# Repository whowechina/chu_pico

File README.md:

# Chu Pico - Chunithm Style Mini Controller
[点这里可以切换到中文版](README_CN.md)

Features:
* It's small, made for 15-17 inch screen.
* Air towers are replaced with built-in ToF sensors.
* Traditional IR Air mechanism is also provided for DIYers.
* HID lights, of course!
* 32 keys (upper and lower rows).
* Follows CrazyRedMachine's RedBoard I/O protocol.
* Command line of rich features.
* All source files open.

Thanks to many respectful guys/companies who made their tools or materials free or open source (KiCad, OnShape, InkScape, Raspberry things).

And thanks to community developers that inspired me and helped me: CrazyRedMachine (https://github.com/CrazyRedMachine), SpeedyPotato (https://github.com/speedypotato).

And also:
* RP_Silicon_KiCad: https://github.com/HeadBoffin/RP_Silicon_KiCad
* Type-C: https://github.com/ai03-2725/Type-C.pretty

## My Other Projects
You can check out my other cool projects.

* Popn Pico: https://github.com/whowechina/popn_pico
* IIDX Pico: https://github.com/whowechina/iidx_pico
* Chu Pico: https://github.com/whowechina/chu_pico
* Mai Pico: https://github.com/whowechina/mai_pico
* Diva Pico: https://github.com/whowechina/diva_pico
* AIC Pico: https://github.com/whowechina/aic_pico
* Groove Pico: https://github.com/whowechina/groove_pico
* Geki Pico: https://github.com/whowechina/geki_pico
* Musec Pico: https://github.com/whowechina/musec_pico
* Ju Pico: https://github.com/whowechina/ju_pico
* Bishi Pico: https://github.com/whowechina/bishi_pico
* Nos Pico: https://github.com/whowechina/nos_pico
* Voltex Pico: https://github.com/whowechina/voltex_pico
* Chord Pico: https://github.com/whowechina/chord_pico
* Dance Pico: https://github.com/whowechina/dance_pico
* Arcade Pico: https://github.com/whowechina/arcade_pico

## **Disclaimer** ##
I made this project in my personal time with no financial benefit or sponsorship. I will continue to improve the project. I have done my best to ensure that everything is accurate and functional, there's always a chance that mistakes may occur. I cannot be held responsible for any loss of your time or money that may result from using this open source project. Thank you for your understanding.

## About the License
It's CC-NC. So DIY for yourself and for your friend, don't make money from it. And plagiarism that doesn’t even dare to mention the original author is not acceptable. Please note that pooling orders and group buying for raw materials is acceptable.Selling any leftover components at cost (without profit) is also acceptable.

If you're interested in buying from me, or for commercial use, please contact me (Discord, QQ group, Goofish).
* My Discord Invitation: https://discord.gg/M8f2PPQFEA
* QQ Group: 854535476
* Goofish: whowe12345

## HOW TO BUILD
### Frequently Made Mistakes
Many DIY enthusiasts commonly make certain mistakes during the building process. Please proceed with extra caution to avoid these.
* **MISTAKE: Soldering everything together without conducting intermediate testing.**  
  Remember, even professional engineers can make mistakes. It becomes significantly harder to identify the root cause of a problem when all components are already assembled or soldered. Therefore, it's advisable to solder and test in stages. The firmware is designed to function correctly even with some components missing, which is good for testing.
* **MISTAKE: Neglecting to cut the ADDR pin trace on the MPR121 module.**  
  The MPR121 module in the market has the ADDR pin pre-connected to ground. But the board expects a floating ADDR pin, otherwise the ADDR pin will short the circuit. Please verify your "CUT" using a multimeter.
* **MISTAKE: Rushing to replace components when something fails.**  
  Sometimes people prematurely assumes that the Raspberry Pi Pico or other modules are faulty.
  Be aware that desoldering and soldering large SMD components is a challenging task. It carries the risk of damaging the component or the PCB board. Patience and caution are crucial. Look at the schematics and PCB design files and ask help from community first. Questioning the integrity of these components should be your last resort.
* **MISTAKE: Failing to properly solder the 2 USB pins of the Raspberry Pi Pico.**  
  These pins are at the bottom side of the PCB. It's a common oversight to either forget to solder them or to leave air bubbles during the process. To avoid this, solder slowly from one side of the hole, using minimal solder wire and a generous amount of flux.

### PCB
* Go JLCPCB and make order with the gerber zip file (latest `Production\PCB\chu_main_xxx.zip`), regular FR-4 board, black color, thickness is **1.6mm**.  
* 1x Rasberry Pico Pi Pico or Pico W.  
  https://www.raspberrypi.com/products/raspberry-pi-pico
  Becareful of 3 pins that are at the other side, they're difficult to solder and may leave air bubbles.  

* 1x USB Type-C socket (918-418K2023S40001 or KH-TYPE-C-16P)
* 36x WS2812B-4020 side-facing RGB LEDs.  
  https://www.lcsc.com/product-detail/Light-Emitting-Diodes-LED_Worldsemi-WS2812B-4020_C965557.html
* TCA9548APWR (TSSOP-24) I2C multiplexer.  
  https://www.lcsc.com/product-detail/Signal-Switches-Encoders-Decoders-Multiplexers_Texas-Instruments-TCA9548APWR_C130026.html
* 3x MPR121 modules, there're many types in the market, choose ones like this.  
  https://www.sparkfun.com/products/retired/9695  
  Before solder MP121 module to the main PCB board, remember to use a knife to **cut (unshort) the tiny trace that connects ADDR to the GND**. Please be careful not to cut more than necessary.  
    
  There's not enough space for the whole height of MPR121 module plus the lead pads. So you need to solder the module like the picture shows below.  
  First apply some insulation tape.  
    
  Then solder the module directly against the PCB.  
    
  You can use the pins comes with the module, but you need to cut away the plastic pads.  
  
* 5x Sharp GP2Y0E03 or ST VL53L0X ToF sensor modules, you need cables as well. Please note that the pictures are taken from older version of PCB, the LEDs have been changed to side-facing ones.  
  https://www.lcsc.com/product-detail/Angle-Linear-Position-Sensors_Sharp-Microelectronics-GP2Y0E03_C920270.html  

   You can use both of them in a same PCB, the firmware will identify each of them automatically.  
  
* 12x 0603 5.1kohm resistors for all the resistors on PCB.
* 8x 0603 1uF (0.1~1uF all fine) capacitors (C1 to C8), OPTIONAL, recommended.
* 3x Panasonic EVQP46B3M tiny tactile switches.  
  https://industry.panasonic.com/global/en/products/control/switch/light-touch/number/evqp46b3m

### Light Guide Panel
* Find a service to cut a light guide panel using DXF or DWG file `Production\CAD\chu_pico_lgp.*`, the size is 256mm*60mm, 1.8mm to 2.0mm thickness, thinner is better for sensitivity. 2.0mm is easy to find, 1.8mm is rare. I used 1.8mm for my build.  
  
* LGP material choices:
  * Real LGP (Light Guide Panel) material, it's the best choice.  
    
  * Clear Acrylic with Light Guide Film, it's a good choice.  
    
  * Clear Acrylic with single-side-frosted, it's a good choice.  
    
  * Clear Acrylic with manual single-side-sanding, it can work too.  

### Panel Film
* A self-adhesive **textured**/**frosted** film sheet, it is applied on top surface of the light guide panel. It improves touch feel. You can use window sticker film. It **MUST** be self-adhesive ones, **NOT** static cling ones. They're usually very cheap.
* Cut the film to roughly match the shape of the light guide panel, and stick to the panel.  
  
* Gentlely rub the film to remove any air bubbles and make it stick tightly.  

###  IR Cover
* It's for good looking, as it hides 5 ToF sensors.   
  
* IR lights can go through.  
  
* Find a service to cut an IR cover using the DXF or DWG file `Production\CAD\chu_pico_ir_cover.*`, the size is 293.2mm*63.5mm, 1mm thickness. The material must be "Infrared Transmitting Acrylic Sheet" which can block visible lights (so it looks black) while letting IR lights go through.  
  
* If you can't find one, cut a regular smooth surface acrylic, but it can't hide the ToF sensors which are not good looking.
* If you're using the VL53L0x ToF sensor, please add padding beneath the sensor. This brings it closer to the acrylic cover, which can prevent acrosstalk error.

### 3D Printing
* You need a Bambu 3D printer for 2 reasons:
  * Parts are designed to perfectly fit in its 256mm*256mm print bed.
  * Its AMS system works great for easy-to-remove support material.
* For all the following prints:
  * To fit object in the bed, Z rotate: 315 degree, X, Y move to: 134mm  

  * PLA, PETG, ABS are all OK.
  * Layer height: 0.2mm
  * 4-6 walls, 50+% infill
  * Support: No (unless specified).

* Base: `Production\3D\chu_pico_base.stl`, dark gray filament, turn on support to have better screw holes.
* Cover: `Production\3D\chu_pico_cover(_aime).stl`, dark gray filament, print up-side down.
* Cover Base: `Production\3D\chu_pico_cover_base.stl`, **clear transparent (IMPORTANT)** filament.
* Light Guide Panel Fixer: `Production\3D\chu_pico_lgp_fixer.stl`, color doesn't matter. Note that in newer revisions, it has been integrated into the base.

### Exploded View for Assembly

From top to bottom:
* IR Cover
* Cover
* Cover Base
* Panel Film
* Light Guide Panel
* PCB
* Light Guide Panel Fixer (integrated into the base in newer revisions)
* Base

Notes:
* You need **4x M3\*12mm screws and 4x M3 hex nuts** to fix the housing.
* You need **4x M2\*6mm screws** for extra fixation for the lgp area of the housing.
* If you use the `_insert` version of the cover, you also need **4x M2\*3mm\*3mm heatset inserts**.

7x silicone anti-slip pads can be applied to the bottom side of the base to provide stability when playing.  

### IR Air Tower
This is not necessary for Chu Pico. But some people may prefer the traditional IR air tower, especially when they're using Chu Pico design for a full-sized controller.
So hereby I provide the IR air tower design, with a pair of air tower PCBs and the firmware support.
1. First, you need to order the sensor PCBs, the gerber file is `Production\PCB\chu_air_v*.zip`. It's for both sides of the air tower.
2. Solder components to the PCB following the silkscreen. About the components, see the notes below.
3. For left side PCB, use J1 to connect to the Raspberry Pi Pico, and for the right side PCB, use J2. GPIO 3 -> A, GPIO 4 -> B, GPIO 5 -> C, ADC 0 (GPIO 26) -> Right S, ADC 1 (GPIO 27) -> Left S.  

4. Steps for deployment.
   * Enable IR sensor in the firmware (command `ir enable`), this will disable ToF.
   * Enable diagnostics for IR (command `ir diagnostic`).
   * Orientation of the PCB: for the left side PCB, its J1 is at the lowest, for the right side PCB, its J2 is at the lowest (up-side-down).
   * Place the air towers and watch the output of the diagnostics, higher value means beam is received.
   * Set the baseline after the towers are properly placed (command `ir baseline`).
   * Optionally, set the sensitivity, it's a percentage of expected change (command `ir trigger <1..100>`).

#### Notes for the Components
* D1, D2, D3 are IR333C-A IR LEDs;
* Q2, Q4, Q6 are PT333-3B phototransistors.
* Q1, Q3, Q5 are N-Channel MOSFETs with low Rds, such as AO3400, see calculations below.
* R2, R4, R6 are current limiting resistors, see calculations below.
* R1, R3, R5 are mosfet gate resistors, 10ohm is fine.
* R7, R8, R9 are pull-up resistors, 2Kohm is fine.
* R10 is a pull-down resistor, 10Kohm is fine.

* Let's do the calculation for D1 as an example. To get proper signal strength, we want about 1A current for it.  
  The current for D1 is calculated by `I = (Vcc - Vf) / (Rds + R2)`. Vcc is 3.3V, Vf is the forward voltage of D1 (about 2.6V@1A). For a low Rds N-Channel MOSFET such as AO3400, Rds is about 0.047ohm, so R2 should be about 0.7ohm to get 1A current. You can use other N-Channel MOSFETs, but you need to calculate the values accordingly.

### Firmware
* UF2 file is in `Production\Firmware` folder.
* For the new build, hold the BOOTSEL button while connect the USB to a PC, there will be a disk named "RPI-RP2" showed up. Drag the UF2 firmware binary file into it. That's it. There's a small hole at the bottom side of the Chu Pico, it is facing right to the BOOTSEL button.
* It works on CrazyRedMachine's RedBoard protocol. For more information, please check out CrazyRedMachine's project (Don't forget to give him a star and drop by his GitHub for other cool projects):  
https://github.com/CrazyRedMachine/RedBoard
* It has a command line to do configuration. You can use this Web Serial Terminal to connect to the USB serial port of the Chu Pico. (Note: "?" is for help)  
  https://googlechromelabs.github.io/serial-terminal/  

## CAD Source File
I'm using OnShape free subscription. It's powerful but it can't archive original designs to local, so I can only share the link here. STL/DXF/DWG files are exported from this online document.  
https://cad.onshape.com/documents/8b9d0fe6ff1bfa4da17d33ee/w/5c7c980a282a19e7ba1db795/e/56ee65492584a3f709c23c49?renderMode=1&uiState=64fd606f17393c0e6f9b19a4

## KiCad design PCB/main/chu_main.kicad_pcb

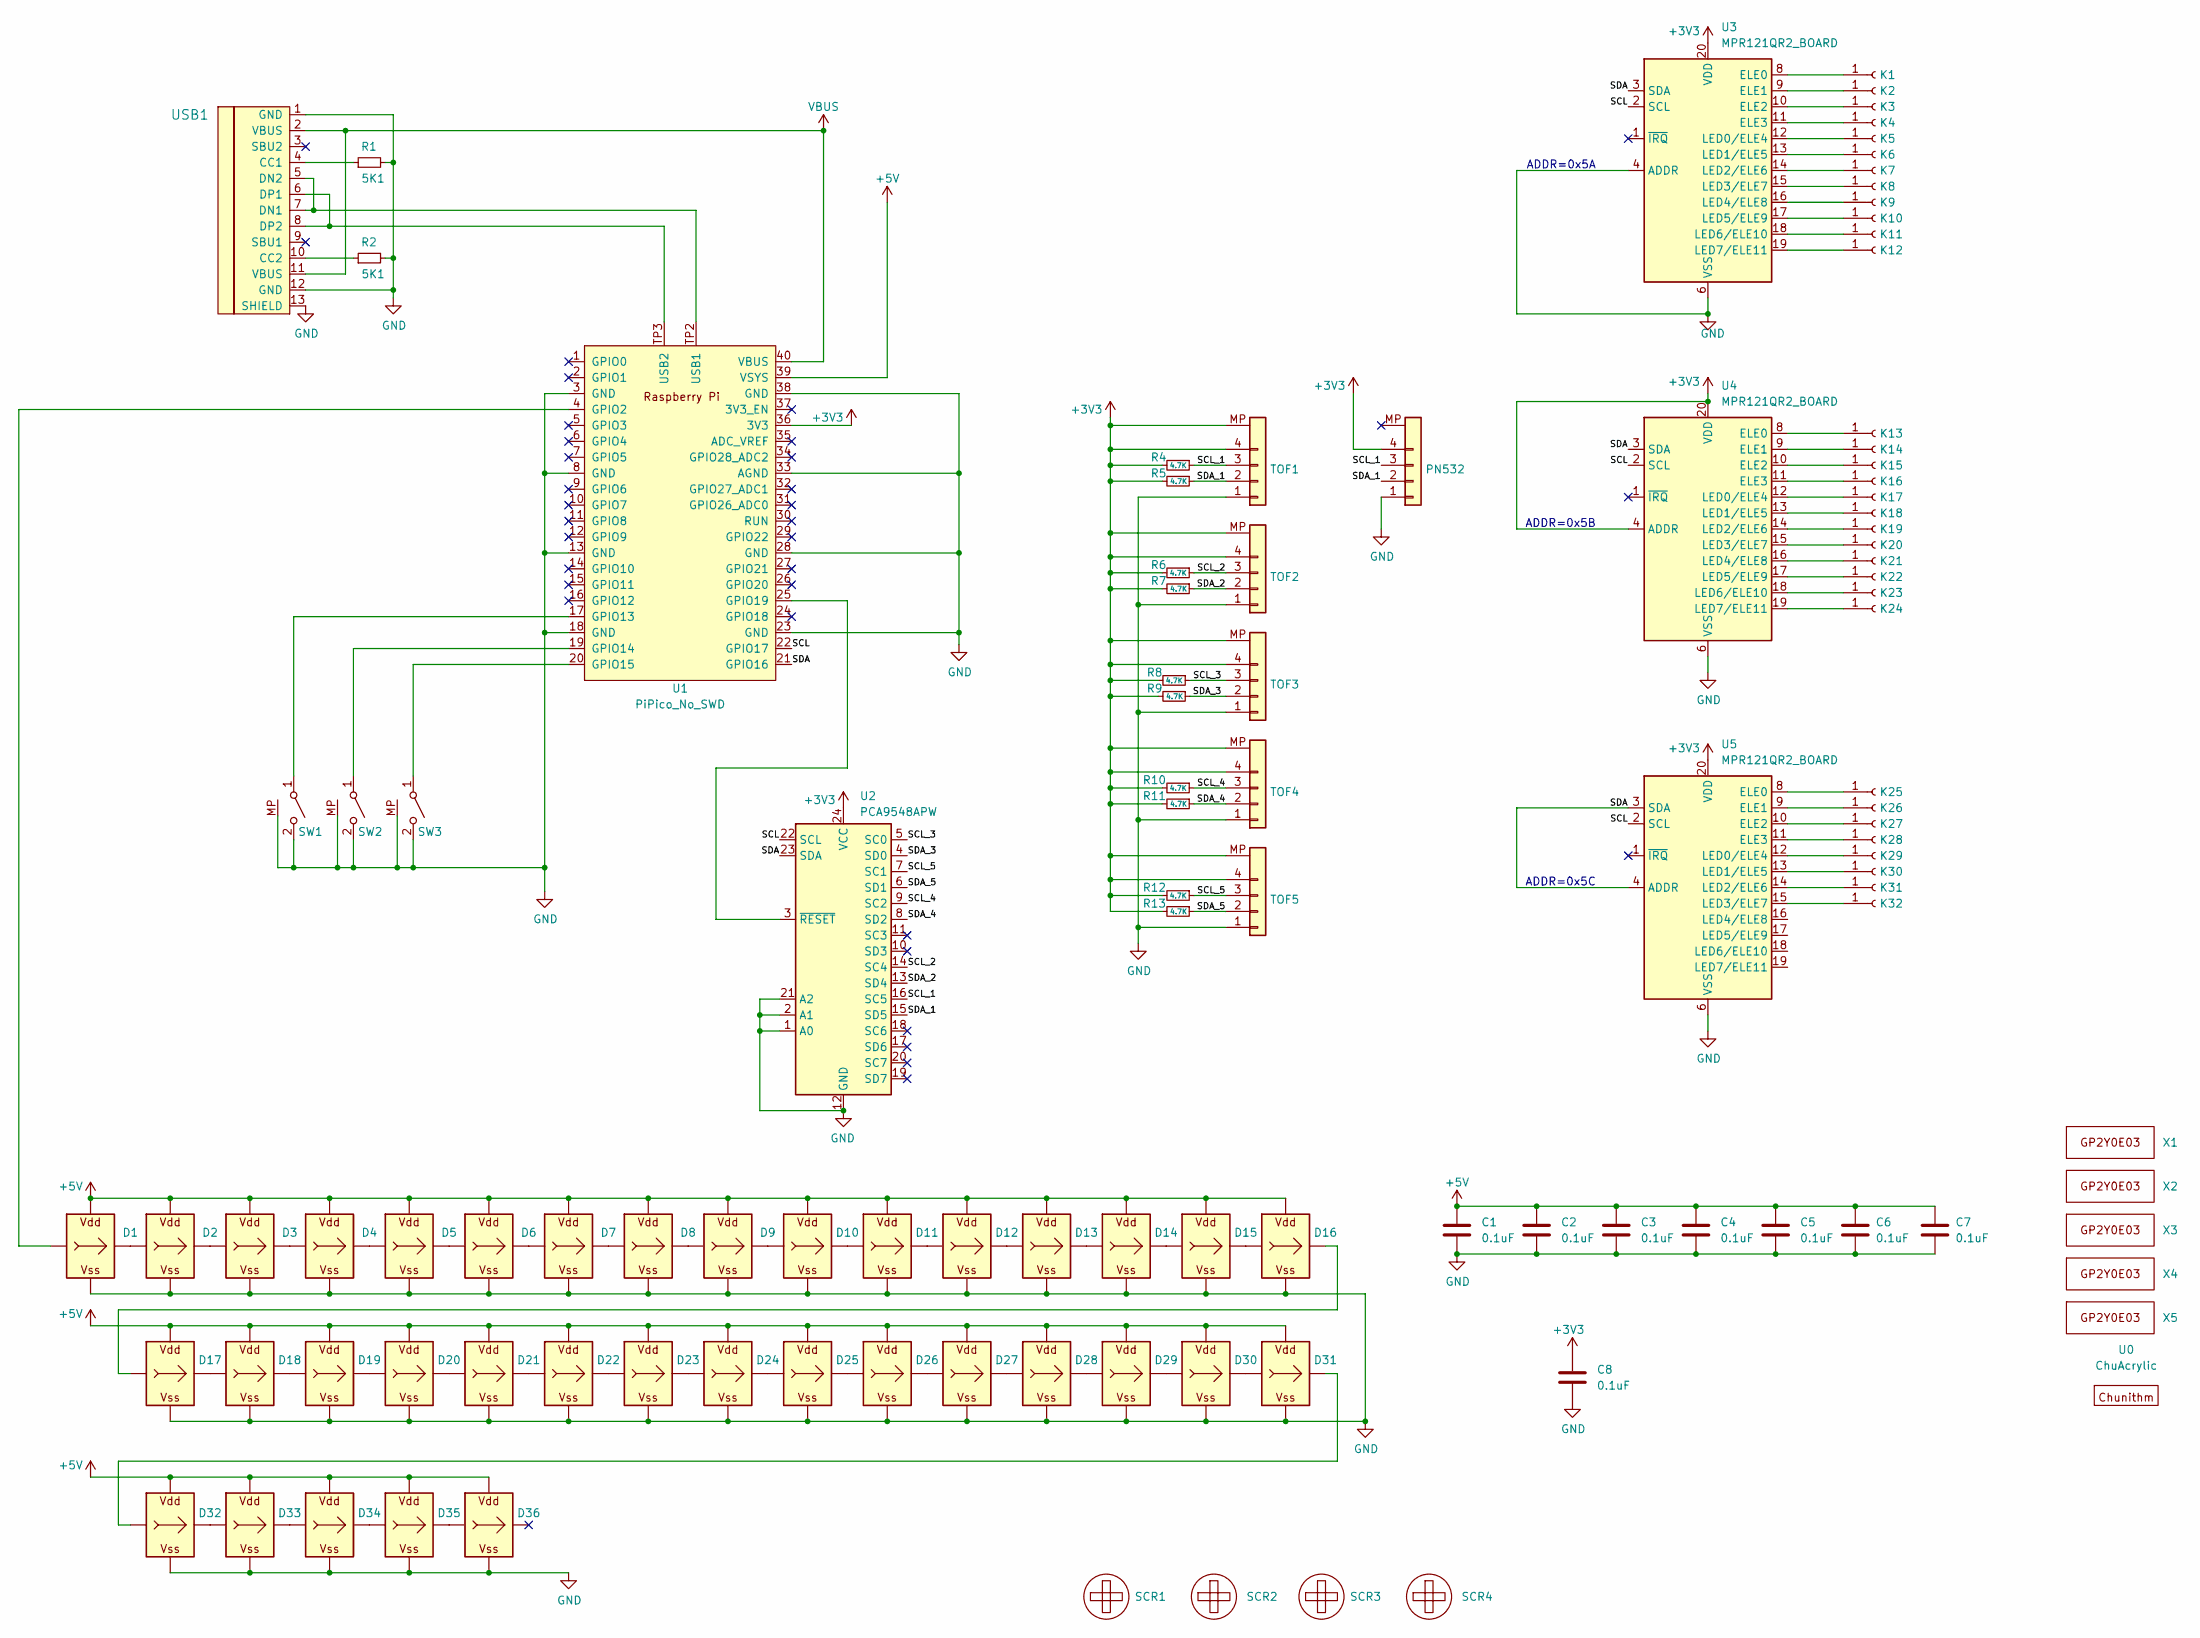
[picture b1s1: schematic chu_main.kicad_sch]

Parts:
C1, C2, C3, C4, C5, C6, C7, C8: 0.1uF; C_0603_1608Metric_Pad1.08x0.95mm_HandSolder
D1, D2, D3, D4, D5, D6, D7, D8, D9, D10, D11, D12, D13, D14, D15, D16, D17, D18, D19, D20, D21, D22, D23, D24, D25, D26, D27, D28, D29, D30, D31, D32, D33, D34, D35, D36: WS2812B_Unified; WS2812B-4020
K1, K2, K3, K4, K5, K6, K7, K8, K9, K10, K15, K16, K17, K18, K19, K20, K21, K22, K27, K28, K29, K30, K31, K32: Conn_01x01_Female; ChuKey
K11, K14, K23, K26: Conn_01x01_Female; ChuKeyBiasLeft
K12, K13, K24, K25: Conn_01x01_Female; ChuKeyBiasRight
PN532: TOF_I2C; SH1.0_4P_Solder_Combo
R1, R2: 5K1; R_0603_1608Metric_Pad0.98x0.95mm_HandSolder; LCSC C23186
R4, R5, R6, R7, R8, R9, R10, R11, R12, R13: 4.7K; R_0603_1608Metric_Pad0.98x0.95mm_HandSolder; LCSC C23186
SCR1, SCR2, SCR3, SCR4: ScrewHole; MountingHole_3.2mm_M3
SW1, SW2, SW3: SPST_EVQP4; SW_EVQ-P46B3M
TOF1, TOF2, TOF3, TOF4, TOF5: TOF_I2C; SH1.0_4P_Solder_Combo
U0: ChuAcrylic
U1: PiPico_No_SWD; RPi_Pico_SMD_Pins_No_SWD
U2: PCA9548APW; TSSOP-24_4.4x7.8mm_P0.65mm
U3, U4, U5: MPR121QR2_BOARD; MPR121_BOARD
USB1: U262-161N-4BVC11; HRO-TYPE-C-31-M-12-Assembly; LCSC C319148
X1, X2, X3, X4, X5: GP2Y0E03_REAL

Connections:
+3V3: C8.1, PN532.4, R4.2, R5.2, R6.2, R7.2, R8.2, R9.2, R10.2, R11.2, R12.2, R13.2, TOF1.4, TOF1.MP, TOF2.4, TOF2.MP, TOF3.4, TOF3.MP, TOF4.4, TOF4.MP, TOF5.4, TOF5.MP, U1.36 (3V3), U2.24 (VCC), U3.20 (VDD), U4.4 (ADDR), U4.20 (VDD), U5.20 (VDD)
+5V: C1.1, C2.1, C3.1, C4.1, C5.1, C6.1, C7.1, D1.V (VDD), D2.V (VDD), D3.V (VDD), D4.V (VDD), D5.V (VDD), D6.V (VDD), D7.V (VDD), D8.V (VDD), D9.V (VDD), D10.V (VDD), D11.V (VDD), D12.V (VDD), D13.V (VDD), D14.V (VDD), D15.V (VDD), D16.V (VDD), D17.V (VDD), D18.V (VDD), D19.V (VDD), D20.V (VDD), D21.V (VDD), D22.V (VDD), D23.V (VDD), D24.V (VDD), D25.V (VDD), D26.V (VDD), D27.V (VDD), D28.V (VDD), D29.V (VDD), D30.V (VDD), D31.V (VDD), D32.V (VDD), D33.V (VDD), D34.V (VDD), D35.V (VDD), D36.V (VDD), U1.39 (VSYS)
/SCL: U1.22 (GPIO17), U2.22 (SCL), U3.2 (SCL), U4.2 (SCL), U5.2 (SCL)
/SCL_1: PN532.3, R4.1, TOF1.3, U2.16 (SC5)
/SCL_2: R6.1, TOF2.3, U2.14 (SC4)
/SCL_3: R8.1, TOF3.3, U2.5 (SC0)
/SCL_4: R10.1, TOF4.3, U2.9 (SC2)
/SCL_5: R12.1, TOF5.3, U2.7 (SC1)
/SDA: U1.21 (GPIO16), U2.23 (SDA), U3.3 (SDA), U4.3 (SDA), U5.3 (SDA), U5.4 (ADDR)
/SDA_1: PN532.2, R5.1, TOF1.2, U2.15 (SD5)
/SDA_2: R7.1, TOF2.2, U2.13 (SD4)
/SDA_3: R9.1, TOF3.2, U2.4 (SD0)
/SDA_4: R11.1, TOF4.2, U2.8 (SD2)
/SDA_5: R13.1, TOF5.2, U2.6 (SD1)
GND: C1.2, C2.2, C3.2, C4.2, C5.2, C6.2, C7.2, C8.2, D1.G (VSS), D2.G (VSS), D3.G (VSS), D4.G (VSS), D5.G (VSS), D6.G (VSS), D7.G (VSS), D8.G (VSS), D9.G (VSS), D10.G (VSS), D11.G (VSS), D12.G (VSS), D13.G (VSS), D14.G (VSS), D15.G (VSS), D16.G (VSS), D17.G (VSS), D18.G (VSS), D19.G (VSS), D20.G (VSS), D21.G (VSS), D22.G (VSS), D23.G (VSS), D24.G (VSS), D25.G (VSS), D26.G (VSS), D27.G (VSS), D28.G (VSS), D29.G (VSS), D30.G (VSS), D31.G (VSS), D32.G (VSS), D33.G (VSS), D34.G (VSS), D35.G (VSS), D36.G (VSS), PN532.1, R1.2, R2.2, SW1.2 (B), SW1.MP, SW2.2 (B), SW2.MP, SW3.2 (B), SW3.MP, TOF1.1, TOF2.1, TOF3.1, TOF4.1, TOF5.1, U1.3 (GND), U1.8 (GND), U1.13 (GND), U1.18 (GND), U1.23 (GND), U1.28 (GND), U1.33 (AGND), U1.38 (GND), U2.1 (A0), U2.2 (A1), U2.12 (GND), U2.21 (A2), U3.4 (ADDR), U3.6 (VSS), U4.6 (VSS), U5.6 (VSS), USB1.1 (GND), USB1.12 (GND), USB1.13 (SHIELD)
unnamed: D1.I (In), U1.4 (GPIO2)
unnamed: D1.O (Out), D2.I (In)
unnamed: D2.O (Out), D3.I (In)
unnamed: D3.O (Out), D4.I (In)
unnamed: D4.O (Out), D5.I (In)
unnamed: D5.O (Out), D6.I (In)
unnamed: D6.O (Out), D7.I (In)
unnamed: D7.O (Out), D8.I (In)
unnamed: D8.O (Out), D9.I (In)
unnamed: D9.O (Out), D10.I (In)
unnamed: D10.O (Out), D11.I (In)
unnamed: D11.O (Out), D12.I (In)
unnamed: D12.O (Out), D13.I (In)
unnamed: D13.O (Out), D14.I (In)
unnamed: D14.O (Out), D15.I (In)
unnamed: D15.O (Out), D16.I (In)
unnamed: D16.O (Out), D17.I (In)
unnamed: D17.O (Out), D18.I (In)
unnamed: D18.O (Out), D19.I (In)
unnamed: D19.O (Out), D20.I (In)
unnamed: D20.O (Out), D21.I (In)
unnamed: D21.O (Out), D22.I (In)
unnamed: D22.O (Out), D23.I (In)
unnamed: D23.O (Out), D24.I (In)
unnamed: D24.O (Out), D25.I (In)
unnamed: D25.O (Out), D26.I (In)
unnamed: D26.O (Out), D27.I (In)
unnamed: D27.O (Out), D28.I (In)
unnamed: D28.O (Out), D29.I (In)
unnamed: D29.O (Out), D30.I (In)
unnamed: D30.O (Out), D31.I (In)
unnamed: D31.O (Out), D32.I (In)
unnamed: D32.O (Out), D33.I (In)
unnamed: D33.O (Out), D34.I (In)
unnamed: D34.O (Out), D35.I (In)
unnamed: D35.O (Out), D36.I (In)
unnamed: K1.1, U3.8 (ELE0)
unnamed: K2.1, U3.9 (ELE1)
unnamed: K3.1, U3.10 (ELE2)
unnamed: K4.1, U3.11 (ELE3)
unnamed: K5.1, U3.12 (LED0/ELE4)
unnamed: K6.1, U3.13 (LED1/ELE5)
unnamed: K7.1, U3.14 (LED2/ELE6)
unnamed: K8.1, U3.15 (LED3/ELE7)
unnamed: K9.1, U3.16 (LED4/ELE8)
unnamed: K10.1, U3.17 (LED5/ELE9)
unnamed: K11.1, U3.18 (LED6/ELE10)
unnamed: K12.1, U3.19 (LED7/ELE11)
unnamed: K13.1, U4.8 (ELE0)
unnamed: K14.1, U4.9 (ELE1)
unnamed: K15.1, U4.10 (ELE2)
unnamed: K16.1, U4.11 (ELE3)
unnamed: K17.1, U4.12 (LED0/ELE4)
unnamed: K18.1, U4.13 (LED1/ELE5)
unnamed: K19.1, U4.14 (LED2/ELE6)
unnamed: K20.1, U4.15 (LED3/ELE7)
unnamed: K21.1, U4.16 (LED4/ELE8)
unnamed: K22.1, U4.17 (LED5/ELE9)
unnamed: K23.1, U4.18 (LED6/ELE10)
unnamed: K24.1, U4.19 (LED7/ELE11)
unnamed: K25.1, U5.8 (ELE0)
unnamed: K26.1, U5.9 (ELE1)
unnamed: K27.1, U5.10 (ELE2)
unnamed: K28.1, U5.11 (ELE3)
unnamed: K29.1, U5.12 (LED0/ELE4)
unnamed: K30.1, U5.13 (LED1/ELE5)
unnamed: K31.1, U5.14 (LED2/ELE6)
unnamed: K32.1, U5.15 (LED3/ELE7)
unnamed: SW1.1 (A), U1.17 (GPIO13)
unnamed: SW2.1 (A), U1.19 (GPIO14)
unnamed: SW3.1 (A), U1.20 (GPIO15)
unnamed: U1.25 (GPIO19), U2.3 (~RESET)
unnamed: U1.TP2 (USB1), USB1.5 (DN2), USB1.7 (DN1)
unnamed: U1.TP3 (USB2), USB1.6 (DP1), USB1.8 (DP2)
unnamed: R1.1, USB1.4 (CC1)
unnamed: R2.1, USB1.10 (CC2)
VBUS: U1.40 (VBUS), USB1.2 (VBUS), USB1.11 (VBUS)

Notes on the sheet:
ADDR=0x5C
ADDR=0x5A
ADDR=0x5B

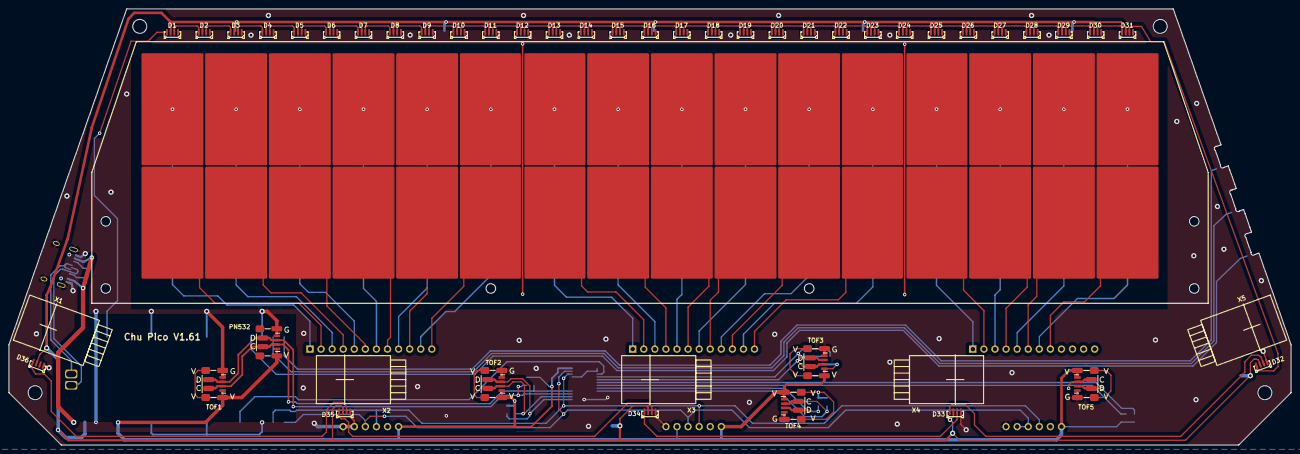
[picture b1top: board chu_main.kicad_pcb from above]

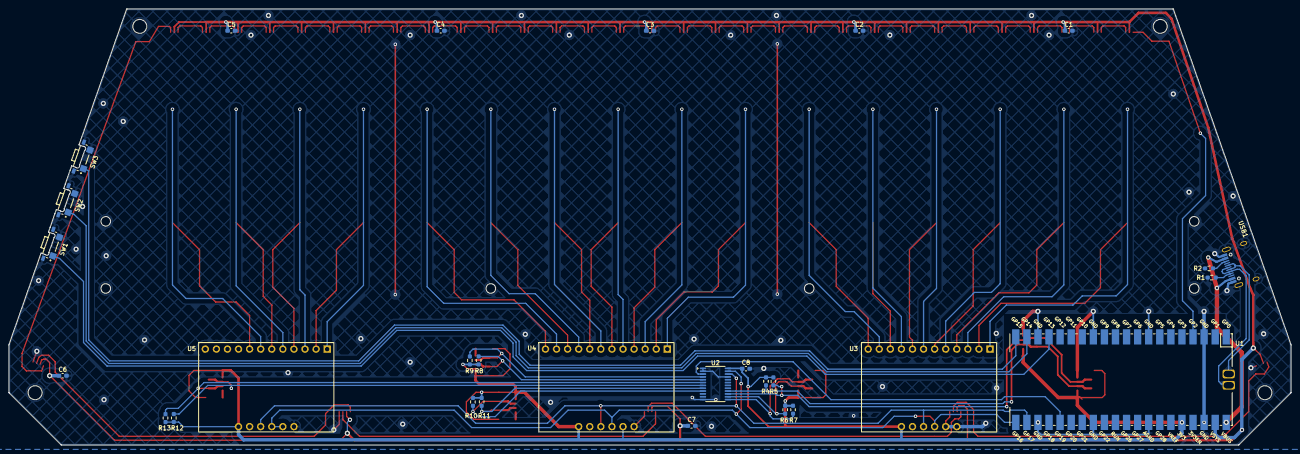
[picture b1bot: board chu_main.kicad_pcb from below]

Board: 2 copper layers, 294.0 x 100.0 mm, 113 parts (29 on the bottom side), 92 nets.

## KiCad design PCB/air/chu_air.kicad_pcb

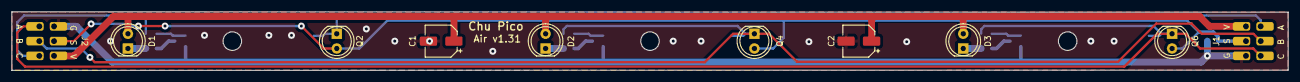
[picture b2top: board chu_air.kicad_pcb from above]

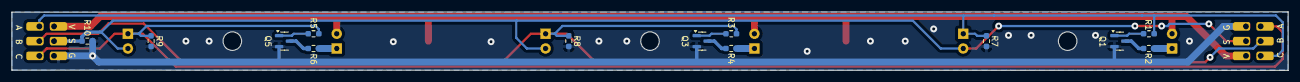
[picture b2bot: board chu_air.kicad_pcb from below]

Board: 2 copper layers, 220.0 x 10.1 mm, 23 parts (13 on the bottom side), 15 nets.

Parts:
C1, C2: 47uF; CP_Elec_5x5.9
D1, D2, D3: IR26-21C_L110_TR8; LED_D5.0mm_IRGrey
J1, J2: Conn_01x06_Socket; 6P_Air_Conn
Q1, Q3, Q5: 2N7002; SOT-23
Q2, Q4, Q6: Q_Photo_NPN; LED_D5.0mm_IRBlack
R1, R3, R5: 10R; R_0603_1608Metric_Pad0.98x0.95mm_HandSolder
R2, R4, R6: 1R; R_0603_1608Metric_Pad0.98x0.95mm_HandSolder
R7, R8, R9: 2K; R_0603_1608Metric_Pad0.98x0.95mm_HandSolder
R10: 10K; R_0603_1608Metric_Pad0.98x0.95mm_HandSolder

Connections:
+3.3V: C1.1, C2.1, D1.2 (A), D2.2 (A), D3.2 (A), J1.4, J2.4
/A: J1.1, J2.1, Q2.1 (C), R1.1, R7.1
/B: J1.2, J2.2, Q4.1 (C), R3.1, R8.1
/C: J1.3, J2.3, Q6.1 (C), R5.1, R9.1
/SIG: J1.5, J2.5, Q2.2 (E), Q4.2 (E), Q6.2 (E), R10.1
GND: C1.2, C2.2, J1.6, J2.6, Q1.2 (S), Q3.2 (S), Q5.2 (S), R7.2, R8.2, R9.2, R10.2
unnamed: D1.1 (K), R2.2
unnamed: D2.1 (K), R4.2
unnamed: D3.1 (K), R6.2
unnamed: Q1.3 (D), R2.1
unnamed: Q1.1 (G), R1.2
unnamed: Q3.3 (D), R4.1
unnamed: Q3.1 (G), R3.2
unnamed: Q5.3 (D), R6.1
unnamed: Q5.1 (G), R5.2

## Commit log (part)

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2023-08-09 Work started, PCB shape and keyboard sensor done
2023-08-13 Some updates (keypad, IR sensor firmware)
2023-08-18 Layout progress 40%
2023-08-19 Layoug progress 70%
2023-08-27 PCB v1 done
2023-09-02 Firmware progress 30%
2023-09-03 Firmware progress 50%
2023-09-05 Firmware progress 70%, some HID part works
2023-09-06 Small progress (issue in 2nd interface)
2023-09-07 Some fix in descriptors
2023-09-07 Small progress, USB working now.
2023-09-09 PCB v1.1 (LED footprint update)
2023-09-09 PCB v1.2 (finetune capsense pad size)
2023-09-09 Firmware done, I call it beta
2023-09-10 Ready to publish
2023-09-10 Small fix before publish
2023-09-10 Minor README fix
2023-09-10 More tolerance screw holes in base
2023-09-10 Small updates to the README
2023-09-10 Better LGP fixer height
2023-09-10 GP2Y0E03 is actually from Sharp
2023-09-10 Add timeout to I2C operations, so more stable
2023-09-10 More silicone pads
2023-09-10 Fix missing pad image
2023-09-10 NKRO interface added
2023-09-10 NKRO USB desc works but logic not there yet
2023-09-11 NKRO working but keymap is not configurable
2023-09-11 NKRO with Umiguri default keymap (always on)
2023-09-14 Fix cmake copy destination
2023-09-14 Update comment on LGP thinkness
2023-09-16 Temporary disable nkro report
2023-09-16 Optimization on stability
2023-09-16 Overclock for best latency (still stable)
2023-09-16 Update readme for overclock I2C
2023-09-16 Finetune PCB and CAD files
2023-09-16 Add 17inch in README
2023-09-16 Command line functional but not completed
2023-09-17 More command lines
2023-09-17 More working command lines
2023-09-17 Fix some typo
2023-09-17 A little case CAD finetune
2023-09-17 README update with command line and other fixes
2023-09-18 Attempt on VL53L0X (not working)
2023-09-19 VL53L0x driver integrated but not fully tested
2023-09-21 VL53L0X and GP2Y0E03 both supported
2023-09-21 Faster baseline update
2023-09-21 Some optimization
2023-09-21 Explicitly identify both TOF
2023-09-22 Use MPR121 internal logic now
2023-09-22 Some cleanups
2023-09-23 Better response when sliding
2023-09-23 Lower chance freezing when saving
2023-09-23 cli allows abbreviation when no ambiguity
2023-09-23 filter settings added
2023-09-23 Better defaults
2023-09-23 Better tof distance calc
2023-09-23 ToF default value optimized
2023-09-24 Update README on MPR121 soldering
2023-09-27 More command line info and case insensitive
2023-09-27 Get MPR121's max sensitivity
2023-09-27 More commands
2023-09-27 Backspace support in command line
2023-09-28 SFI, FFI and ESI config
2023-09-28 Enable HID joy if redboard feature received
2023-09-28 LED brightness config
2023-09-29 CLI refactoring
2023-10-02 Readme update
2023-10-03 Readme update on Bambu printer
2023-10-06 Add LED test firmware
2023-10-06 PN532 code started.
2023-10-09 gp2y0e distance calculation correction
2023-10-14 Crossreference to Mai Pico
2023-10-15 PCB v1.4 (reduce crosstalk)
2023-10-15 Update README on ToF and MPR121
2023-10-15 Better baseline keeping
2023-10-17 PN532 Small Antenna Attempt
2023-10-21 AIME carder reader option in CAD files
2023-10-21 Temporary NFC debug command
2023-10-21 PCB v1.5 for dedicate PN532 pads
2023-10-22 SN display in CLI
2023-10-22 AIME reader (50%, not working)
2023-10-23 AIME reader (60%, works a little bit)
2023-10-24 AIME reader (70%, felica encap refactored)
2023-10-25 AIME reader (75%, felica read works)
2023-10-25 AIME reader (80%, felica card works)
2023-10-28 AIME reader (85%, felica card works correctly)
2023-10-29 Virtual AIC Working
2023-11-05 Update command in CLI
2023-11-15 Upload Redboard binaries
2023-11-15 Remove old test binaries
2023-11-19 Fix VL53L0X timeout issue
2023-11-19 Fix USB failure due to VL53L0x wait
2023-11-19 VL53L0x update but still crosstalks and shortsight
2023-11-20 VL53L0x with "shortsight" issue, NFC included
2023-11-22 VL53L0x "shortsighted" fixed
2023-11-22 Firmware update with AIME and ToF fix
2023-12-09 Fix minor buffer over read issue
2023-12-09 Fix a misleading image
2023-12-10 Minor lint fix for PCB project
2023-12-10 Cautions in README
2023-12-10 Better timing, I think
2023-12-10 Again better timing
2024-01-12 Better resistor values
2024-03-03 README in Chinese
2024-03-03 Optimizations to README
2024-03-03 Optimize README
2024-03-16 Use aic_pico as a library via submodule
2024-03-17 Attach to latest aic pico
2024-03-29 IR based air module PCB
2024-04-05 Display NFC module in CLI
2024-04-06 Optimize AIME commands
2024-04-24 Cleanup headers
2024-04-24 Update to latest AIC Pico library
2024-04-30 Update to latest aic pico lib
2024-04-30 Minor code cleanup
2024-04-30 Update to latest aic lib and fix random aime issue
2024-04-30 Some cleanup
2024-05-03 Fix minor cmake build issue
2024-05-20 Cmake optimization with built time display
2024-06-04 Remove chu_air PCB as it's not ready
2024-07-15 Cross-reference to new Groove Pico
2024-08-27 Added bevel to the LGP fixer to make room for R1/R2
2024-09-01 Fix level not saved
2024-09-05 Thanks to some projects
2024-09-05 Remove unrelated projects from thanks
2024-09-08 Another attempt of chu air
2024-09-19 Air PCB v1.3
2024-09-19 IR tower (not tested)
2024-09-20 Update component models in air PCB
2024-09-23 IR air tower support
2024-09-23 Some format issue fix
2024-09-23 Fighting with GitHub markdown
2024-09-23 Still fighting
2024-09-23 Fighting continues
2024-09-23 Why?
2024-09-23 Air PCB orientation
2024-09-26 Air PCB v1.31 (update screw clearance)
2024-10-02 Cross-reference and license part update
2024-10-18 Cross-reference and Discord invitation
2024-11-02 Upload missing picture of air pcb
2024-11-02 Fix air key ordering
2024-11-13 Cross-reference to Ju Pico
2024-11-17 CLI welcome message
2024-11-17 Sensor status in raw command
2024-11-23 Cross-reference
2024-11-27 Fix unhandled serial input error code
2024-11-29 Support latest pico sdk
2024-12-02 Fix getchar return handling
2024-12-02 Fix i2c write timing
2024-12-23 Minor update with cross-ref to bishi pico
2024-12-23 Tweak option to skip splitter LED
2024-12-27 Chu main PCB v1.6
2025-01-04 Support for 3 aux buttons
2025-01-04 Better polling rate
2025-01-18 fix: address overflow and persistance bugs with filter config
2025-02-03 Fix typo in `slider.c` and `slider.h`
2025-02-03 Minor change for previous filter bug fix
2025-02-03 Optimize HID report scheme (edge triggering)
2025-02-03 Core 0 fps to 1000
2025-02-03 Sync to latest aic pico library
2025-02-13 Housing supports 3 aux buttons
2025-02-13 3 aux buttons in README
2025-02-16 Fix minor interference in housing base
2025-02-18 PCB v1.61 (fix TOF silkscreen marks)
2025-02-23 Forced report every 4ms for redboard
2025-02-25 Forced update for nkro
2025-03-02 Fix sensor status display
2025-04-04 Cross-reference to Nos Pico
2025-05-16 Remove incorrect file
2025-05-16 Notes on LEDs in older PCB
2025-06-01 Add usb clearance to base, add light shade to cover
2025-07-29 Reset buffer before reading MPR121
2026-01-21 Comments on IR components
2026-03-11 Larger pads and minor updates
2026-03-23 Sync to latest aic pico lib
2026-03-30 Faster IR slew rate to minimize mosfet gray zone time
2026-04-19 Lower ir duty cycle
2026-06-02 Fix interference between cover and support
2026-06-02 Description of extra screws
